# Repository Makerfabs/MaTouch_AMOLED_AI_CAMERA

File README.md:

# MaTouch_AMOLED_AI_CAMERA

## Introduction

The "MaTouch_AMOLED_AI_CAMERA" is a high-definition integrated display, touch and vision sensing product built around the ESP32-S3 chip with built-in Wi-Fi function. It retains a high-quality 1.8-inch AMOLED screen featuring outstanding high contrast ratio and rich color saturation, delivering ultra-clear, vivid and delicate display effects for diverse visual interaction scenarios. Equipped with the professional CTS820 touch chip, it achieves more sensitive, accurate and stable touch response, effectively optimizing daily operation and human-computer interaction experience. Furthermore, the product integrates a high-performance OV3660 CMOS camera module with 3-megapixel high resolution, supporting multiple image output formats and automatic image optimization functions including automatic exposure control and automatic white balance. With excellent low-light imaging performance and high pixel fidelity, it enables clear and stable image capture, visual recognition and AI vision analysis, greatly expanding the product’s application boundaries in embedded vision, intelligent monitoring, interactive shooting and AI scenario development.

Product Link: [MaTouch_AMOLED_AI_CAMERA]

Wiki Link: [MaTouch_AMOLED_AI_CAMERA](https://wiki.makerfabs.com/MaTouch_AMOLED_AI_CAMERA.html)

Example：1.[Display_Touch_Camera_Test](https://wiki.makerfabs.com/MaTouch_AMOLED_AI_CAMERA.html#41-display_touch_camera_test)

2.[Cat_face_detection](https://wiki.makerfabs.com/MaTouch_AMOLED_AI_CAMERA.html#51-cat_face_detection)

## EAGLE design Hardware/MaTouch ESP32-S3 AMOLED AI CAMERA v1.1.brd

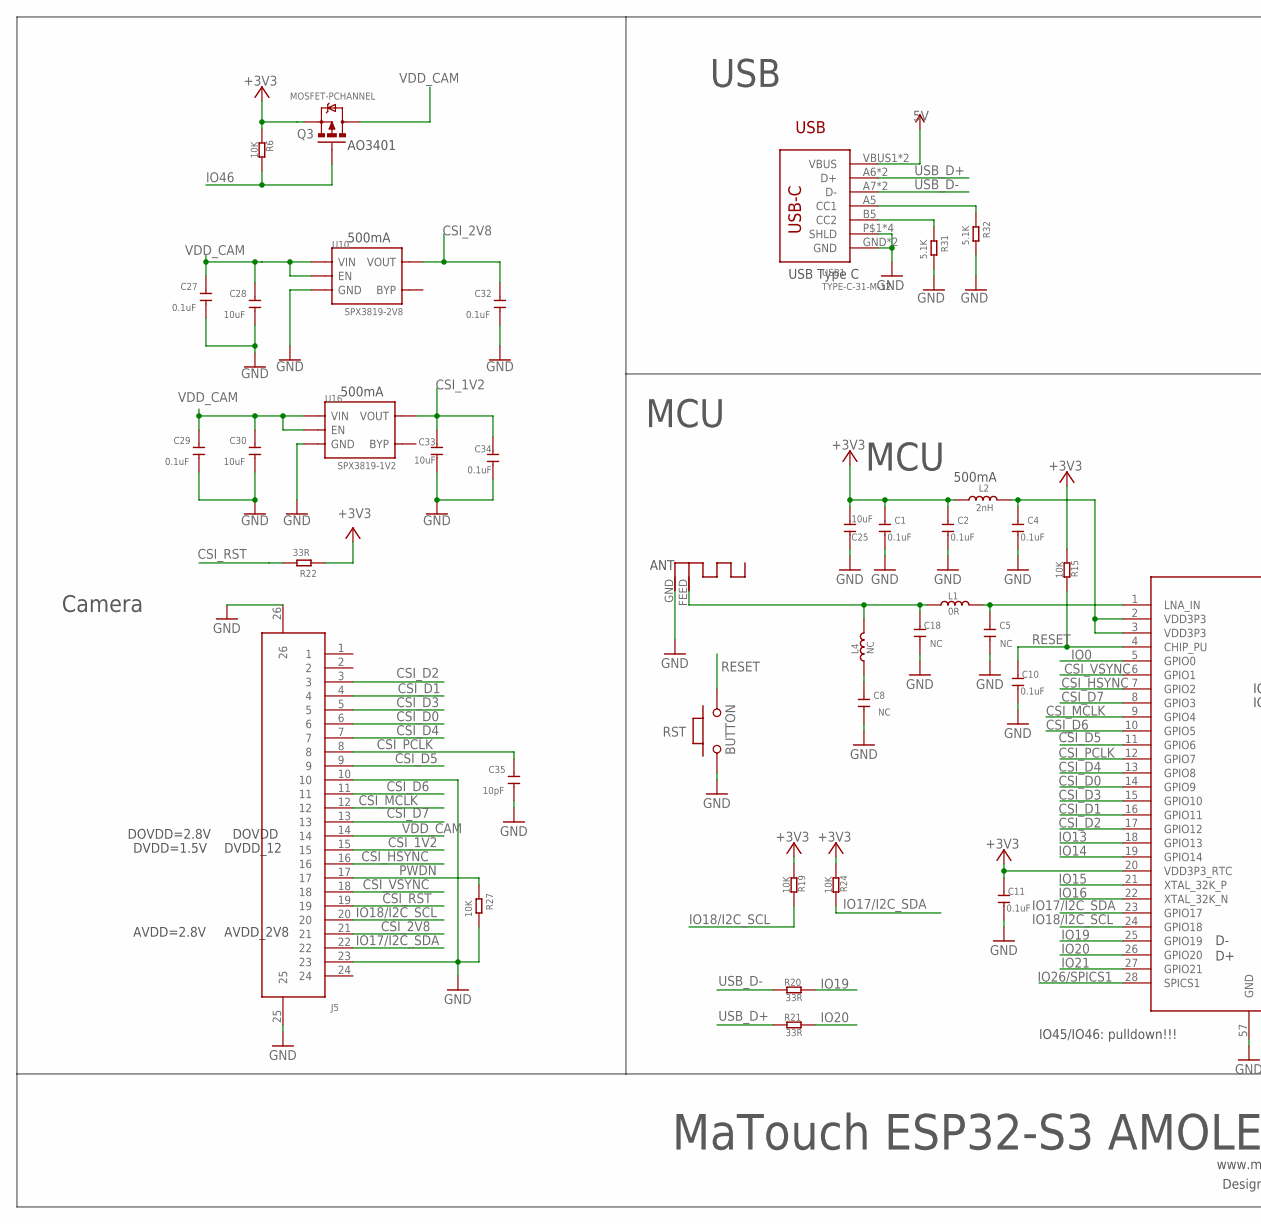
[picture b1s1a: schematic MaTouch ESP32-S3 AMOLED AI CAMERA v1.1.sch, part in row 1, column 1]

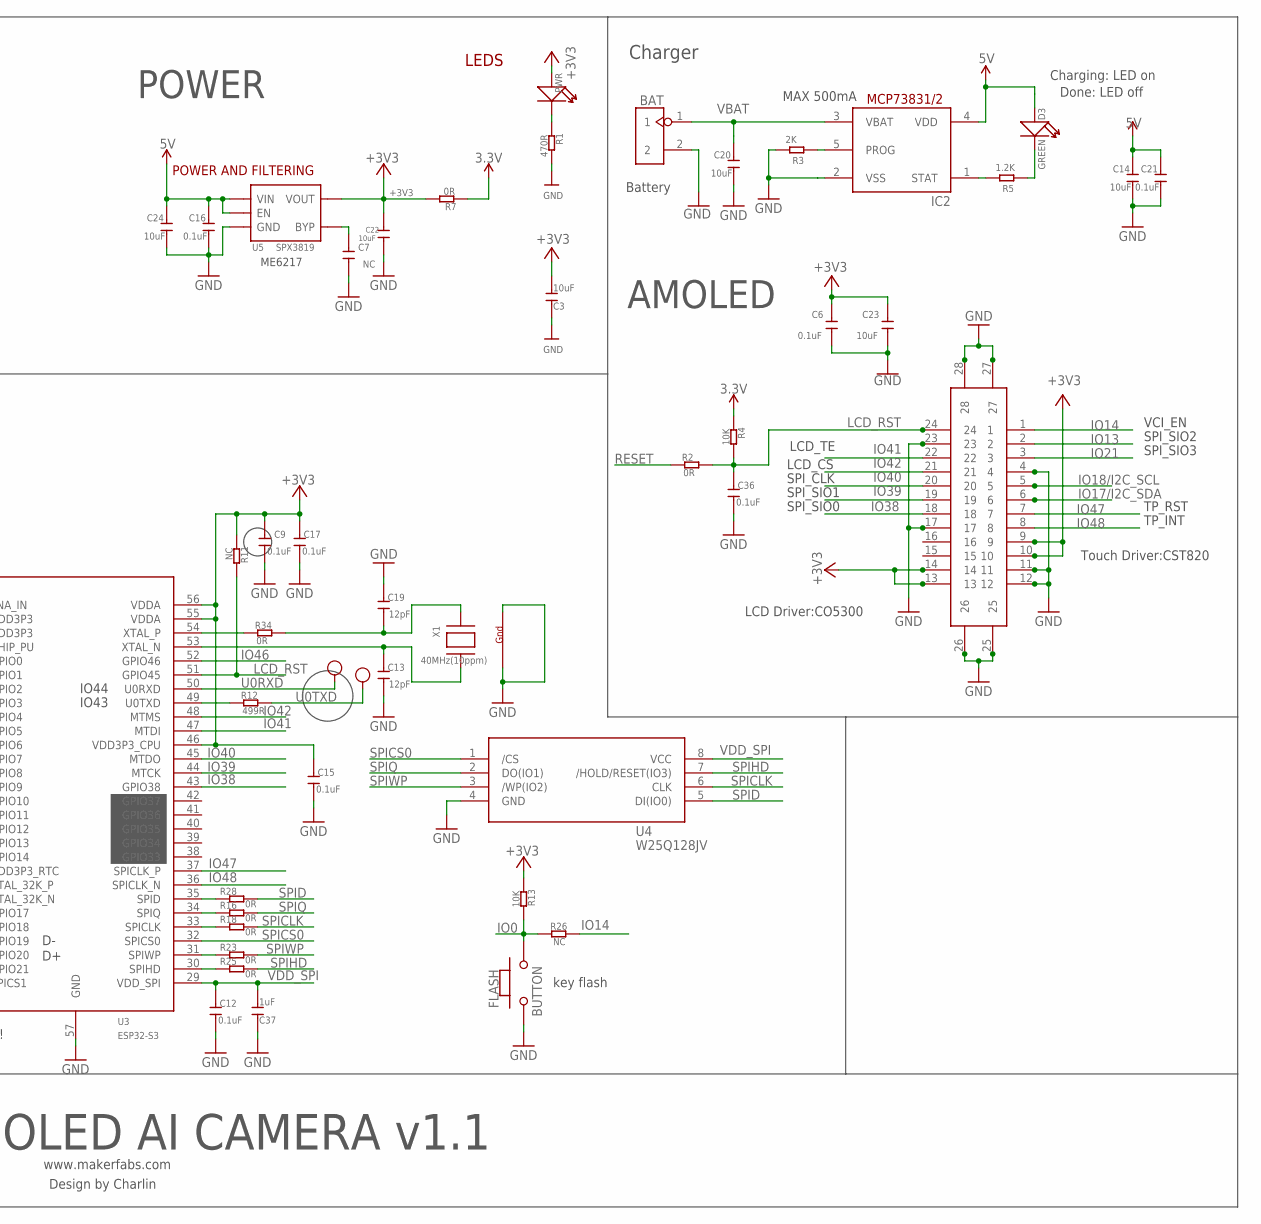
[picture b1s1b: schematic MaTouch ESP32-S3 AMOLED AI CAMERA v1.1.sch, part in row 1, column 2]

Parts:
ANT1: ANTENNA; RN-ANT
BAT: HEADER-2P-2.0; 2P-2.0
C1, C2, C4, C6, C9, C10, C11, C12, C15, C16, C17, C21, C27, C29, C32, C34, C36: 0.1uF; DISCRETE_C0402
C3, C25: 10uF; DISCRETE_C0603
C5, C7, C8, C18: NC; DISCRETE_C0402
C13, C19: 12pF; DISCRETE_C0402
C14, C20, C23, C24, C28, C30, C33: 10uF; DISCRETE_C0402
C22: 10uF; 0603
C35: 10pF; DISCRETE_C0402
C37: 1uF; DISCRETE_C0603
D3: GREEN; DISCRETE_LED-0603
FLASH: BUTTON; 157SW
IC2: TP4054; SOT23-5L
J1: OK-14GF024-04/AXE524127; SMD24-50P-730L250W77H
J5: FPC-24P; SMD26-50P-1760L450W
L1: 0R; DISCRETE_L0402
L2: 2nH; DISCRETE_L0603
L4: NC; DISCRETE_L0402
PWR: DISCRETE_LED0603; DISCRETE_LED-0603
Q3: MOSFET-PCHANNEL; SOT23-3
R1: 470R; DISCRETE_R0402
R2, R7, R16, R18, R23, R25, R28, R34: 0R; DISCRETE_R0402
R3: 2K; DISCRETE_R0402
R4, R6, R13, R15, R19, R24, R27: 10K; DISCRETE_R0402
R5: 1.2K; DISCRETE_R0402
R11, R26: NC; DISCRETE_R0402
R12: 499R; DISCRETE_R0402
R20, R21, R22: 33R; DISCRETE_R0402
R31, R32: 5.1K; DISCRETE_R0402
RST: BUTTON; 157SW
RX: TEST-POINT'4545'; TP-D45MIL; PARTNO DNP
TX: TEST-POINT'4545'; TP-D45MIL; PARTNO DNP
U3: ESP32-S3; QFN56-7*7MM
U4: W25Q128JV; SOIC-8-208MIL
U5: SPX3819; SOT23-5
U10: SPX3819-2V8; SOT23-5
U16: SPX3819-1V2; SOT23-5
USB1: TYPE-C-31-M-12
X1: 40MHz(10ppm); NX3225

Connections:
3.3V: R4.2, R7.2
5V: C14.2, C16.2, C21.2, C24.2, D3.+, IC2.4 (VDD), U5.1 (VIN), U5.3 (EN), USB1.VBUS1 (VBUS), USB1.VBUS2 (VBUS)
+3V3: C1.2, C2.2, C3.2, C6.2, C9.2, C11.2, C15.2, C17.2, C22.1, C23.2, C25.2, J1.9, J1.10, J1.13, J1.14, L2.1, PWR.+, Q3.2 (S), R6.2, R7.1, R11.2, R13.2, R15.2, R19.2, R22.1, R24.2, U3.20 (VDD3P3_RTC), U3.46 (VDD3P3_CPU), U3.55 (VDDA), U3.56 (VDDA), U5.5 (VOUT)
CSI_1V2: C33.2, C34.2, J5.15, U16.5 (VOUT)
CSI_2V8: C32.2, J5.21, U10.5 (VOUT)
CSI_D0: J5.6, U3.14 (GPIO9)
CSI_D1: J5.4, U3.16 (GPIO11)
CSI_D2: J5.3, U3.17 (GPIO12)
CSI_D3: J5.5, U3.15 (GPIO10)
CSI_D4: J5.7, U3.13 (GPIO8)
CSI_D5: J5.9, U3.11 (GPIO6)
CSI_D6: J5.11, U3.10 (GPIO5)
CSI_D7: J5.13, U3.8 (GPIO3)
CSI_HSYNC: J5.16, U3.7 (GPIO2)
CSI_MCLK: J5.12, U3.9 (GPIO4)
CSI_PCLK: C35.2, J5.8, U3.12 (GPIO7)
CSI_RST: J5.19, R22.2
CSI_VSYNC: J5.18, U3.6 (GPIO1)
GND: ANT1.GND, BAT.2, C1.1, C2.1, C3.1, C4.1, C5.1, C6.1, C7.1, C8.1, C9.1, C10.1, C11.1, C12.1, C13.1, C14.1, C15.1, C16.1, C17.1, C18.1, C19.2, C20.1, C21.1, C22.2, C23.1, C24.1, C25.1, C27.1, C28.1, C29.1, C30.1, C32.1, C33.1, C34.1, C35.1, C36.1, C37.1, FLASH.1, IC2.2 (VSS), J1.4, J1.11, J1.12, J1.17, J1.23, J1.25, J1.26, J1.27, J1.28, J5.10, J5.23, J5.25, J5.26, R1.1, R3.2, R27.2, R31.2, R32.2, RST.1, U3.57 (GND), U4.4 (GND), U5.2 (GND), U10.2 (GND), U16.2 (GND), USB1.GND, USB1.GND2 (GND), USB1.P$1 (SHLD), USB1.P$2 (SHLD), USB1.P$3 (SHLD), USB1.P$4 (SHLD), X1.2 (G2), X1.4 (G1)
IO0: FLASH.2, R13.1, R26.2, U3.5 (GPIO0)
IO13: J1.2, U3.18 (GPIO13)
IO14: J1.1, R26.1, U3.19 (GPIO14)
IO15: U3.21 (XTAL_32K_P)
IO16: U3.22 (XTAL_32K_N)
IO17/I2C_SDA: J1.6, J5.22, R24.1, U3.23 (GPIO17)
IO18/I2C_SCL: J1.5, J5.20, R19.1, U3.24 (GPIO18)
IO19: R20.1, U3.25 (GPIO19)
IO20: R21.1, U3.26 (GPIO20)
IO21: J1.3, U3.27 (GPIO21)
IO26/SPICS1: U3.28 (SPICS1)
IO38: J1.18, U3.43 (GPIO38)
IO39: J1.19, U3.44 (MTCK)
IO40: J1.20, U3.45 (MTDO)
IO41: J1.22, U3.47 (MTDI)
IO42: J1.21, U3.48 (MTMS)
IO46: Q3.1 (G), R6.1, U3.52 (GPIO46)
IO47: J1.7, U3.37 (SPICLK_P)
IO48: J1.8, U3.36 (SPICLK_N)
LCD_RST: C36.2, J1.24, R2.1, R4.1, R11.1, U3.51 (GPIO45)
unnamed: ANT1.FEED, C18.2, L1.1, L4.2
unnamed: C5.2, L1.2, U3.1 (LNA_IN)
unnamed: R28.2, U3.35 (SPID)
unnamed: C8.2, L4.1
unnamed: R32.1, USB1.A5 (CC1)
unnamed: PWR.-, R1.2
unnamed: IC2.5 (PROG), R3.1
unnamed: IC2.1 (STAT), R5.2
unnamed: D3.-, R5.1
unnamed: C4.2, L2.2, U3.2 (VDD3P3), U3.3 (VDD3P3)
unnamed: R31.1, USB1.B5 (CC2)
unnamed: R16.2, U3.34 (SPIQ)
unnamed: R34.2, U3.54 (XTAL_P)
unnamed: R18.2, U3.33 (SPICLK)
unnamed: R23.2, U3.31 (SPIWP)
unnamed: R25.2, U3.30 (SPIHD)
unnamed: R12.2, U3.49 (U0TXD)
unnamed: C13.2, U3.53 (XTAL_N), X1.3 (X2)
unnamed: C19.1, R34.1, X1.1 (X1)
unnamed: C7.2, U5.4 (BYP)
PWDN: J5.17, R27.1
RESET: C10.2, R2.2, R15.1, RST.2, U3.4 (CHIP_PU)
SPICLK: R18.1, U4.6 (CLK)
SPICS0: U3.32 (SPICS0), U4.1 (/CS)
SPID: R28.1, U4.5 (DI(IO0))
SPIHD: R25.1, U4.7 (/HOLD/RESET(IO3))
SPIQ: R16.1, U4.2 (DO(IO1))
SPIWP: R23.1, U4.3 (/WP(IO2))
U0RXD: RX.T, U3.50 (U0RXD)
U0TXD: R12.1, TX.T
USB_D+: R21.2, USB1.A6 (D+), USB1.B6 (D+)
USB_D-: R20.2, USB1.A7 (D-), USB1.B7 (D-)
VBAT: BAT.1, C20.2, IC2.3 (VBAT)
VDD_CAM: C27.2, C28.2, C29.2, C30.2, J5.14, Q3.3 (D), U10.1 (VIN), U10.3 (EN), U16.1 (VIN), U16.3 (EN)
VDD_SPI: C12.2, C37.2, U3.29 (VDD_SPI), U4.8 (VCC)

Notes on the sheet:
www.makerfabs.com
Design by Charlin
LEDS
POWER AND FILTERING
key flash
MaTouch ESP32-S3 AMOLED AI CAMERA v1.1
POWER
MCU
ME6217
500mA
IO45/IO46: pulldown!!!
IO43
IO44
ANT
USB
AMOLED
DVDD=1.5V
AVDD=2.8V
DOVDD=2.8V
Camera
AVDD_2V8
DVDD_12
DOVDD
USB Type C
Battery
Charging: LED on
Done: LED off
Charger
MAX 500mA
AO3401
LCD_TE
LCD_CS
SPI_CLK
SPI_SIO1
SPI_SIO0
TP_INT
TP_RST
SPI_SIO3
SPI_SIO2
VCI_EN

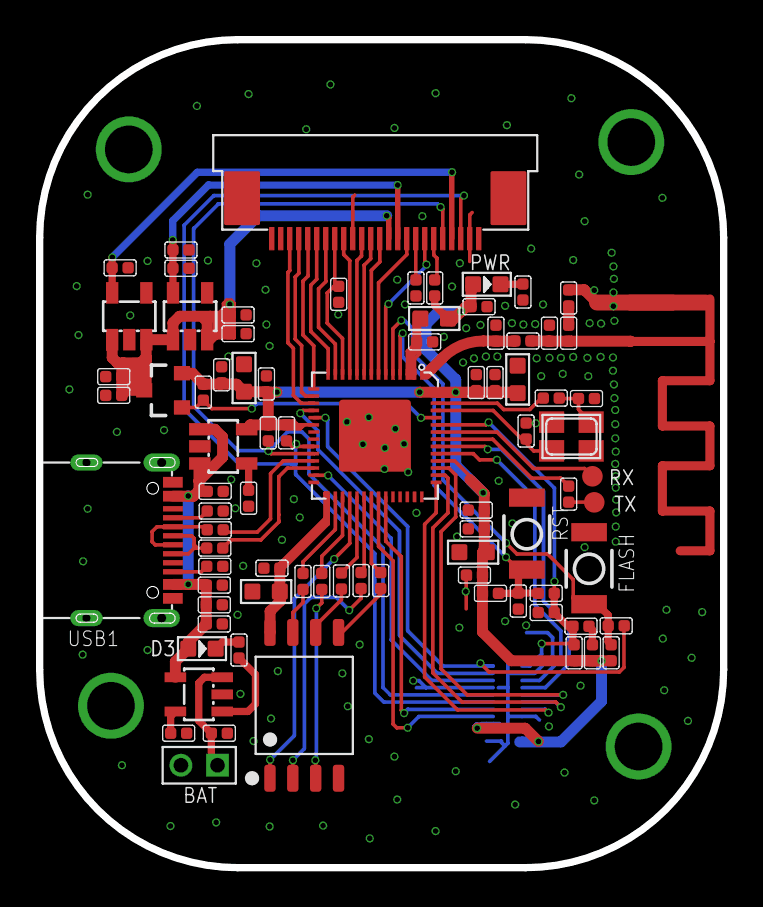
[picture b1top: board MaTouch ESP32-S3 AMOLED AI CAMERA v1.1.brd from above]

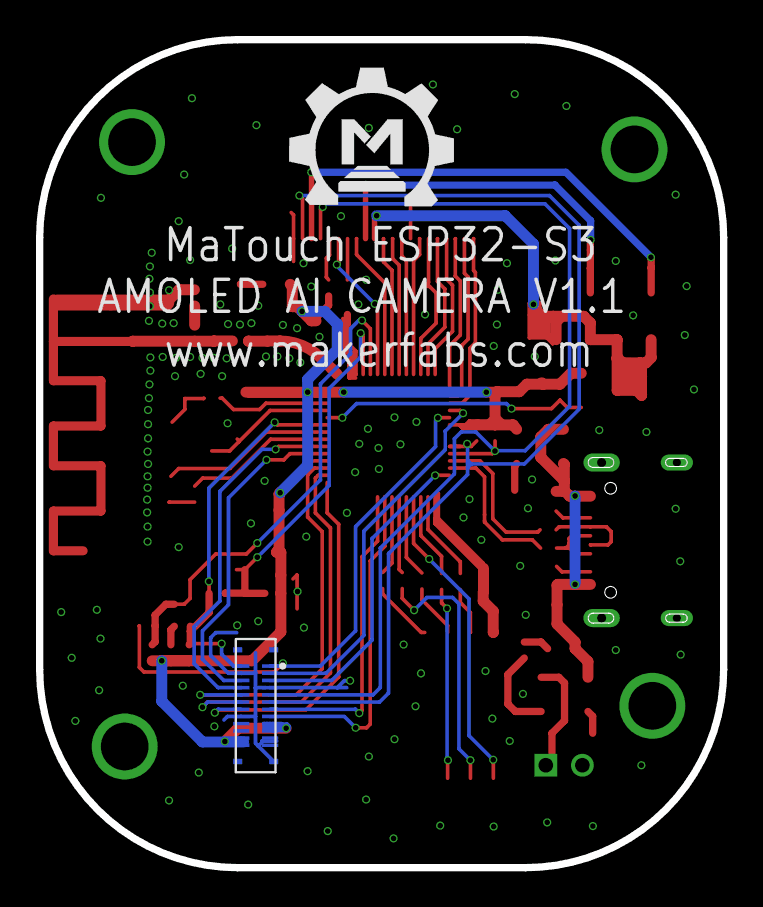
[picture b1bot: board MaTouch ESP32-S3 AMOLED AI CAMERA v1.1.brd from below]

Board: 2 copper layers, 38.0 x 46.0 mm, 84 parts (2 on the bottom side), 71 nets.

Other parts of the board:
U$1: MAKERFABS_0.3

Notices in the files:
parts and their libraries:
User-Submitted: Licensing: Creative Commons ShareAlike 4.0 International - https://creativecommons.org/licenses/by-sa/4.0
microbuilder: This work is placed in the public domain, and may be freely used for commercial and non-commercial work with the following conditions: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
